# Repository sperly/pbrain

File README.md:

# PocketBrain VS Code handoff

Open this folder in VS Code. The [project plan](docs/PocketBrain_Project_Plan.md)
covers the hardware, controls, account model, and firmware behavior.

| Path | What it contains |
|---|---|
| [backend](backend/README.md) | PHP 8.4 dashboard, device API, Realtime client-secret endpoint, and MariaDB migrations |
| [desktop](desktop/README.md) | Python/Tk simulator, microphone and speaker routing, and the direct Realtime client |
| [embedded](embedded/README.md) | CMake/ESP-IDF firmware, bench wiring, and host tests for ESP32-S3 |

This workspace folds the desktop ZIP's PHP add-on into the backend. There
is one PHP API entry point. Existing deployments can deploy this source
while retaining their private configuration and database.

## First development session

1. Run the desktop app in **Demo**, then **Loopback**, using its README.
2. Set up the PHP backend on the HTTPS host. On a fresh database, import
   all four SQL migrations in order. On existing databases, import only
   migrations that have not run, including `003_user_openai_keys.sql` and `004_legal_acceptances.sql`.
   Set DB credentials and a stable application key in the private config.
   Each user adds their OpenAI API key through the dashboard; shared site
   billing requires an explicit opt-in setting.
3. Sign in, pair the desktop simulator, and try one spoken and one muted
   question in **Live**. Check that unlinking the device blocks subsequent
   credential requests.
4. Verify shared conversation history in Live mode. Save a turn, restart the
   simulator, and continue it from History. Pair a second device under the same
   account and check shared history with separate active selections. Disconnect
   after receiving a reply and confirm **Retry save** does not generate another
   answer. Delete a thread and confirm it disappears after the other device syncs.

## Device interface

All paths below are relative to the configured HTTPS base URL. The request
credential is sent in the Authorization bearer header where specified.

| Method and action on api.php | Credential | Current response |
|---|---|---|
| POST pair-start | None | 201 with code, polling_secret, expires_in, poll_interval, and verification_uri |
| POST pair-poll | Polling secret | 202 while awaiting approval, 200 with device_credential when linked, 404 when expired or unknown |
| GET device | Device credential | 200 with id and name, 401 for an invalid or revoked credential |
| POST realtime-secret | Device credential | 200 with value, expires_at, and model, 401 for an invalid or revoked credential |

The simulator records into a 24 kHz, 16-bit mono PCM buffer and opens a new
Realtime WebSocket per turn after Talk is released. Live conversation history
and device selections sync through PHP; each profile keeps a local cache and
one pending recording or completed transcript. Demo and Loopback stay local.
See the backend README for the conversation API and integration tests.

## Verification carried forward

The desktop UI was exercised in Tk. Realtime events and PCM processing
were exercised with mocks. Invite, ownership, and pairing SQL behavior
was checked using a SQLite translation. The PHP 8.4/MariaDB integration,
physical audio devices, and a live OpenAI exchange still need to be
verified on the deployment host and desktop.

ESP-IDF firmware is now in [embedded](embedded/README.md), with build
instructions, configurable bench wiring, and host tests. Physical firmware
validation, custom PCB and enclosure CAD remain subsequent milestones.

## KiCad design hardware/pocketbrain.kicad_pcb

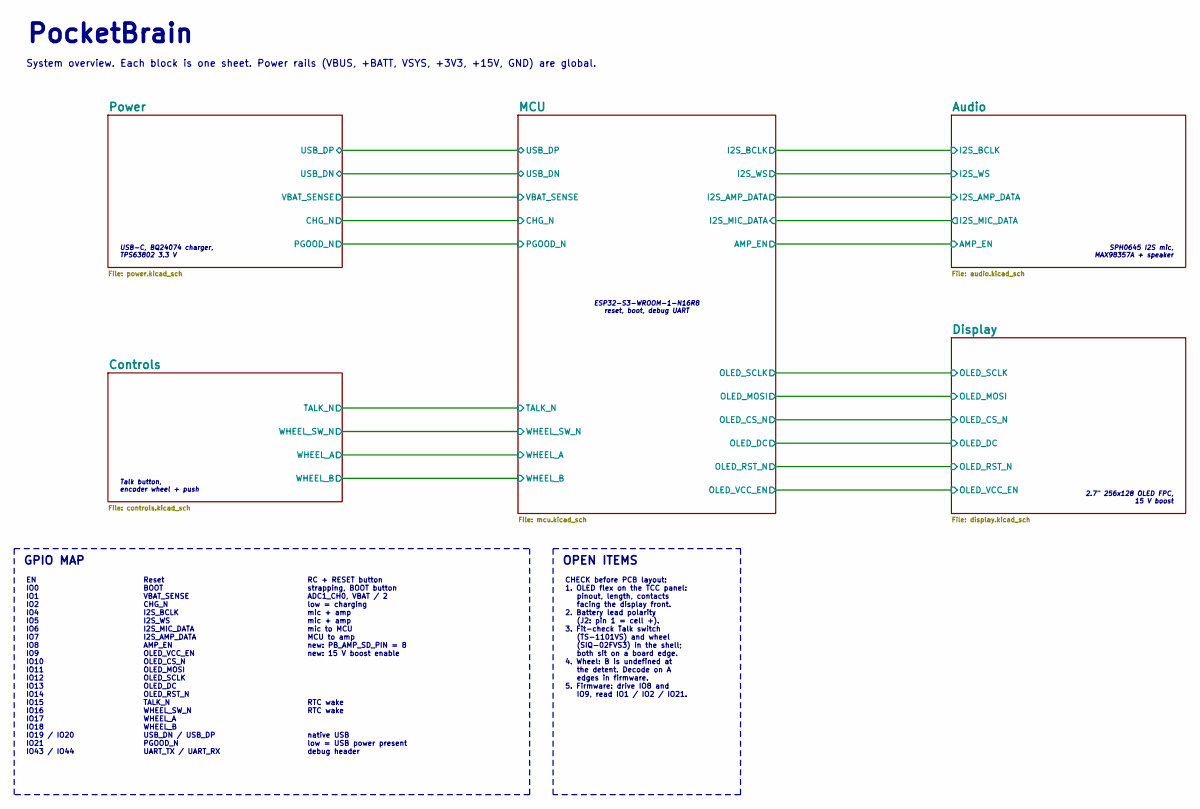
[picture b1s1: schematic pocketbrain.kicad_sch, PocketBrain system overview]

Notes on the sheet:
USB-C, BQ24074 charger, TPS63802 3.3 V
ESP32-S3-WROOM-1-N16R8 reset, boot, debug UART
CHECK before PCB layout: 1. OLED flex on the TCC panel: pinout, length, contacts facing the display front. 2. Battery lead polarity (J2: pin 1 = cell +). 3. Fit-check Talk switch (TS-1101VS) and wheel (SIQ-02FVS3) in the shell; both sit on a board edge. 4. Wheel: B is undefined at the detent. Decod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
Reset BOOT VBAT_SENSE CHG_N I2S_BCLK I2S_WS I2S_MIC_DATA I2S_AMP_DATA AMP_EN OLED_VCC_EN OLED_CS_N OLED_MOSI OLED_SCLK OLED_DC OLED_RST_N TALK_N WHEEL_SW_N WHEEL_A WHEEL_B USB_DN / USB_DP PGOOD_N UART_TX / UART_RX
Talk button, encoder wheel + push
RC + RESET button strapping, BOOT button ADC1_CH0, VBAT / 2 low = charging mic + amp mic + amp mic to MCU MCU to amp new: PB_AMP_SD_PIN = 8 new: 15 V boost enable RTC wake RTC wake native USB low = USB power present debug header
System overview. Each block is one sheet. Power rails (VBUS, +BATT, VSYS, +3V3, +15V, GND) are global.
2.7" 256x128 OLED FPC, 15 V boost
OPEN ITEMS
GPIO MAP
EN IO0 IO1 IO2 IO4 IO5 IO6 IO7 IO8 IO9 IO10 IO11 IO12 IO13 IO14 IO15 IO16 IO17 IO18 IO19 / IO20 IO21 IO43 / IO44
PocketBrain
SPH0645 I2S mic, MAX98357A + speaker

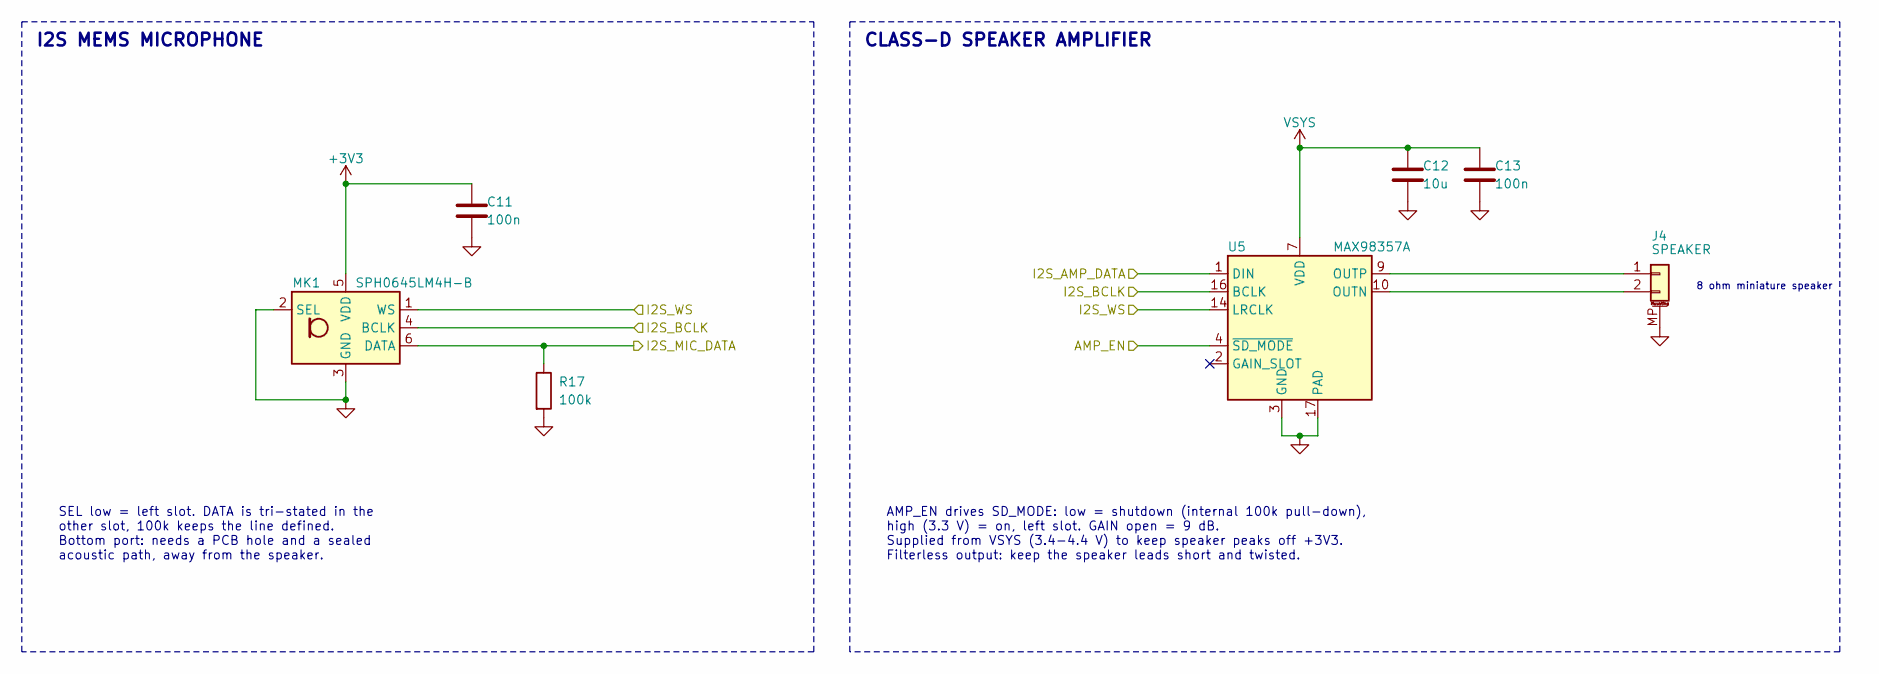
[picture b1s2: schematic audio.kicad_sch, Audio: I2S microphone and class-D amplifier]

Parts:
C11, C13: 100n; C_0402_1005Metric
C12: 10u; C_0603_1608Metric
J4: SPEAKER; JST_SH_BM02B-SRSS-TB_1x02-1MP_P1.00mm_Vertical
MK1: SPH0645LM4H-B; Knowles_SPH0645LM4H-6_3.5x2.65mm
R17: 100k; R_0402_1005Metric
U5: MAX98357A; TQFN-16-1EP_3x3mm_P0.5mm_EP1.23x1.23mm

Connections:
+3V3: C11.1, MK1.5 (VDD); also elsewhere on the board
/Audio/AMP_EN: U5.4 (~SD_MODE); also elsewhere on the board
/Audio/I2S_AMP_DATA: U5.1 (DIN); also elsewhere on the board
/Audio/I2S_BCLK: MK1.4 (BCLK), U5.16 (BCLK); also elsewhere on the board
/Audio/I2S_MIC_DATA: MK1.6 (DATA), R17.1; also elsewhere on the board
/Audio/I2S_WS: MK1.1 (WS), U5.14 (LRCLK); also elsewhere on the board
GND: C11.2, C12.2, C13.2, J4.MP (MountPin), MK1.2 (SEL), MK1.3 (GND), R17.2, U5.3 (GND), U5.11 (GND), U5.15 (GND), U5.17 (PAD); also elsewhere on the board
unnamed: J4.1, U5.9 (OUTP)
unnamed: J4.2, U5.10 (OUTN)
VSYS: C12.1, C13.1, U5.7 (VDD), U5.8 (VDD); also elsewhere on the board

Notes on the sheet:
CLASS-D SPEAKER AMPLIFIER
AMP_EN drives SD_MODE: low = shutdown (internal 100k pull-down), high (3.3 V) = on, left slot. GAIN open = 9 dB. Supplied from VSYS (3.4-4.4 V) to keep speaker peaks off +3V3. Filterless output: keep the speaker leads short and twisted.
8 ohm miniature speaker
I2S MEMS MICROPHONE
SEL low = left slot. DATA is tri-stated in the other slot, 100k keeps the line defined. Bottom port: needs a PCB hole and a sealed acoustic path, away from the speaker.

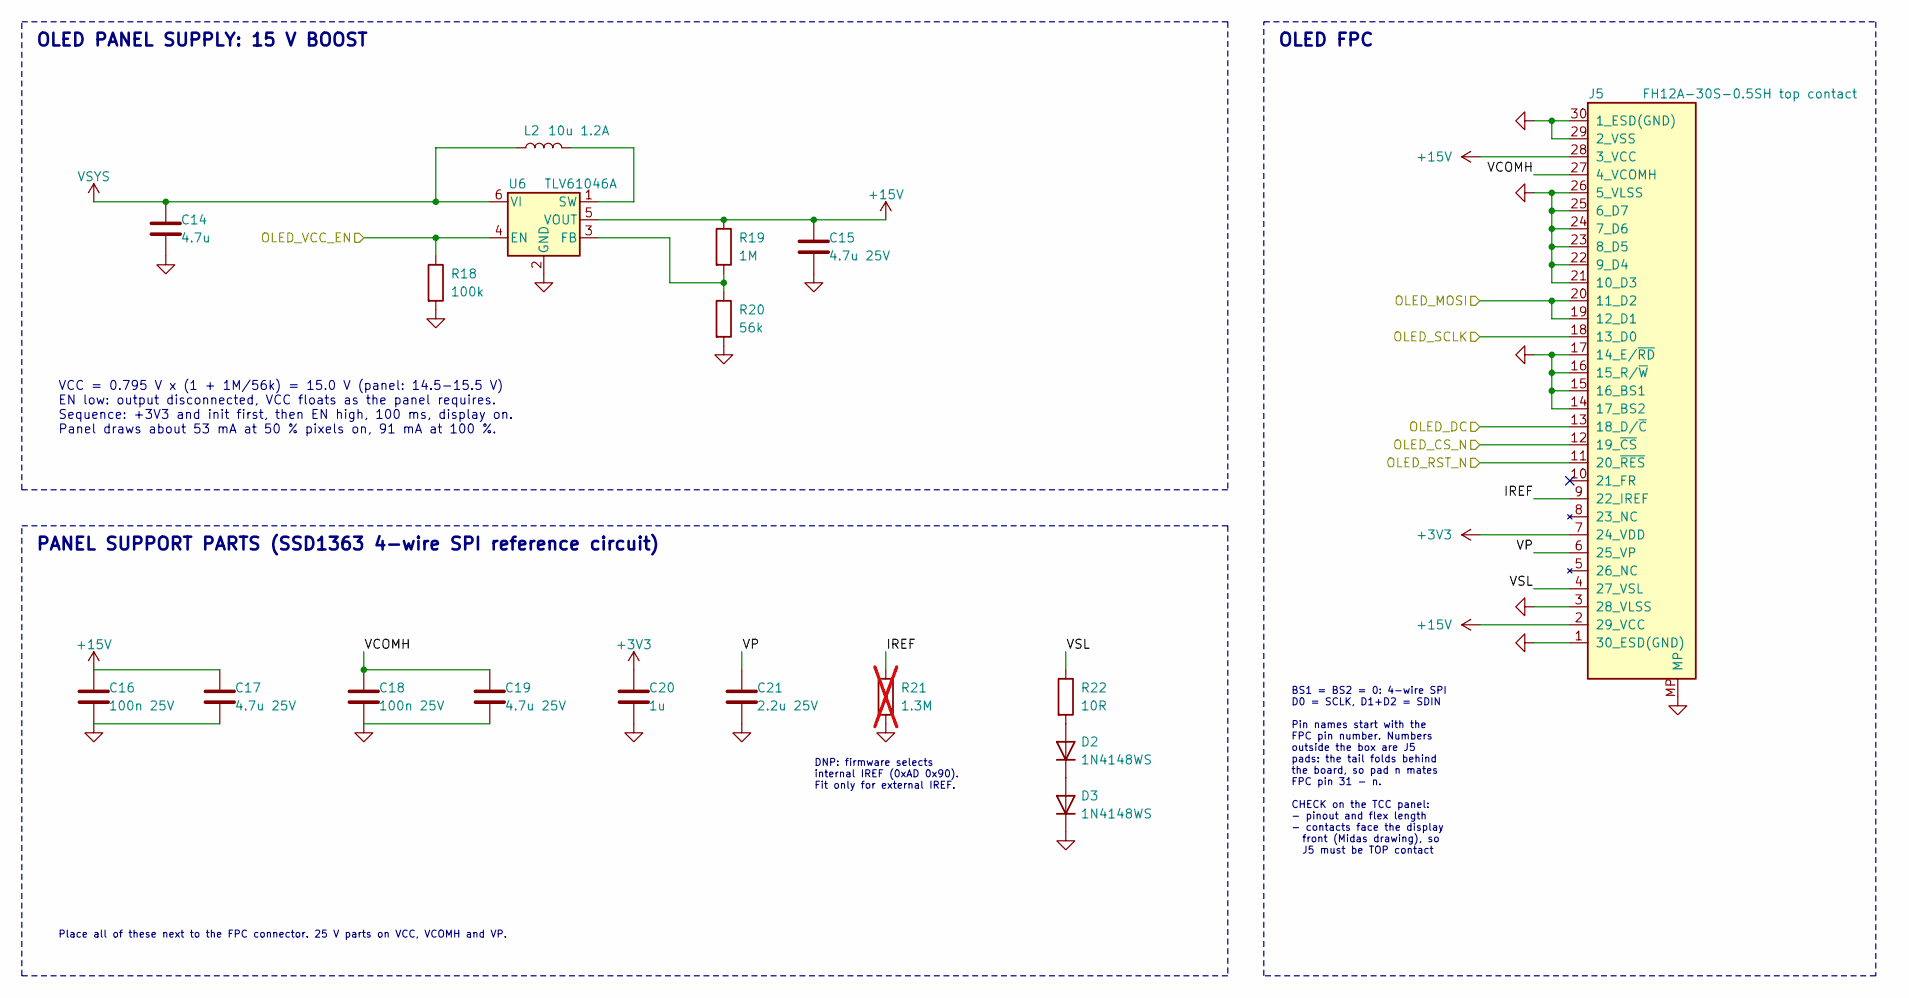
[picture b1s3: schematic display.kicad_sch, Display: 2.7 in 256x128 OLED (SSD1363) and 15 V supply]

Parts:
C14: 4.7u; C_0603_1608Metric
C15, C17, C19: 4.7u 25V; C_0805_2012Metric
C16, C18: 100n 25V; C_0402_1005Metric
C20: 1u; C_0402_1005Metric
C21: 2.2u 25V; C_0603_1608Metric
D2, D3: 1N4148WS; D_SOD-323
J5: FH12A-30S-0.5SH top contact; Hirose_FH12-30S-0.5SH_1x30-1MP_P0.50mm_Horizontal; MPN FH12A-30S-0.5SH(55); LCSC C3036214
L2: 10u 1.2A; L_Taiyo-Yuden_NR-30xx
R18: 100k; R_0402_1005Metric
R19: 1M; R_0402_1005Metric
R20: 56k; R_0402_1005Metric
R21: 1.3M; R_0402_1005Metric; not fitted
R22: 10R; R_0402_1005Metric
U6: TLV61046A; SOT-23-6

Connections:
+3V3: C20.1, J5.7 (24_VDD); also elsewhere on the board
+15V: C15.1, C16.1, C17.1, J5.2 (29_VCC), J5.28 (3_VCC), R19.1, U6.5 (VOUT)
/Display/IREF: J5.9 (22_IREF), R21.1
/Display/OLED_CS_N: J5.12 (19_~CS); also elsewhere on the board
/Display/OLED_DC: J5.13 (18_D/~C); also elsewhere on the board
/Display/OLED_MOSI: J5.19 (12_D1), J5.20 (11_D2); also elsewhere on the board
/Display/OLED_RST_N: J5.11 (20_~RES); also elsewhere on the board
/Display/OLED_SCLK: J5.18 (13_D0); also elsewhere on the board
/Display/OLED_VCC_EN: R18.1, U6.4 (EN); also elsewhere on the board
/Display/VCOMH: C18.1, C19.1, J5.27 (4_VCOMH)
/Display/VP: C21.1, J5.6 (25_VP)
/Display/VSL: J5.4 (27_VSL), R22.1
GND: C14.2, C15.2, C16.2, C17.2, C18.2, C19.2, C20.2, C21.2, D3.1 (K), J5.1 (30_ESD(GND)), J5.3 (28_VLSS), J5.14 (17_BS2), J5.15 (16_BS1), J5.16 (15_R/~W), J5.17 (14_E/~RD), J5.21 (10_D3), J5.22 (9_D4), J5.23 (8_D5), J5.24 (7_D6), J5.25 (6_D7), J5.26 (5_VLSS), J5.29 (2_VSS), J5.30 (1_ESD(GND)), J5.MP, R18.2, R20.2, R21.2, U6.2 (GND); also elsewhere on the board
unnamed: D2.2 (A), R22.2
unnamed: D2.1 (K), D3.2 (A)
unnamed: R19.2, R20.1, U6.3 (FB)
unnamed: L2.2, U6.1 (SW)
VSYS: C14.1, L2.1, U6.6 (VI); also elsewhere on the board

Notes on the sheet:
PANEL SUPPORT PARTS (SSD1363 4-wire SPI reference circuit)
Place all of these next to the FPC connector. 25 V parts on VCC, VCOMH and VP.
BS1 = BS2 = 0: 4-wire SPI D0 = SCLK, D1+D2 = SDIN Pin names start with the FPC pin number. Numbers outside the box are J5 pads: the tail folds behind the board, so pad n mates FPC pin 31 - n. CHECK on the TCC panel: - pinout and flex length - contacts face the display front (Midas drawing), so J5 m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
VCC = 0.795 V x (1 + 1M/56k) = 15.0 V (panel: 14.5-15.5 V) EN low: output disconnected, VCC floats as the panel requires. Sequence: +3V3 and init first, then EN high, 100 ms, display on. Panel draws about 53 mA at 50 % pixels on, 91 mA at 100 %.
DNP: firmware selects internal IREF (0xAD 0x90). Fit only for external IREF.
OLED PANEL SUPPLY: 15 V BOOST
OLED FPC

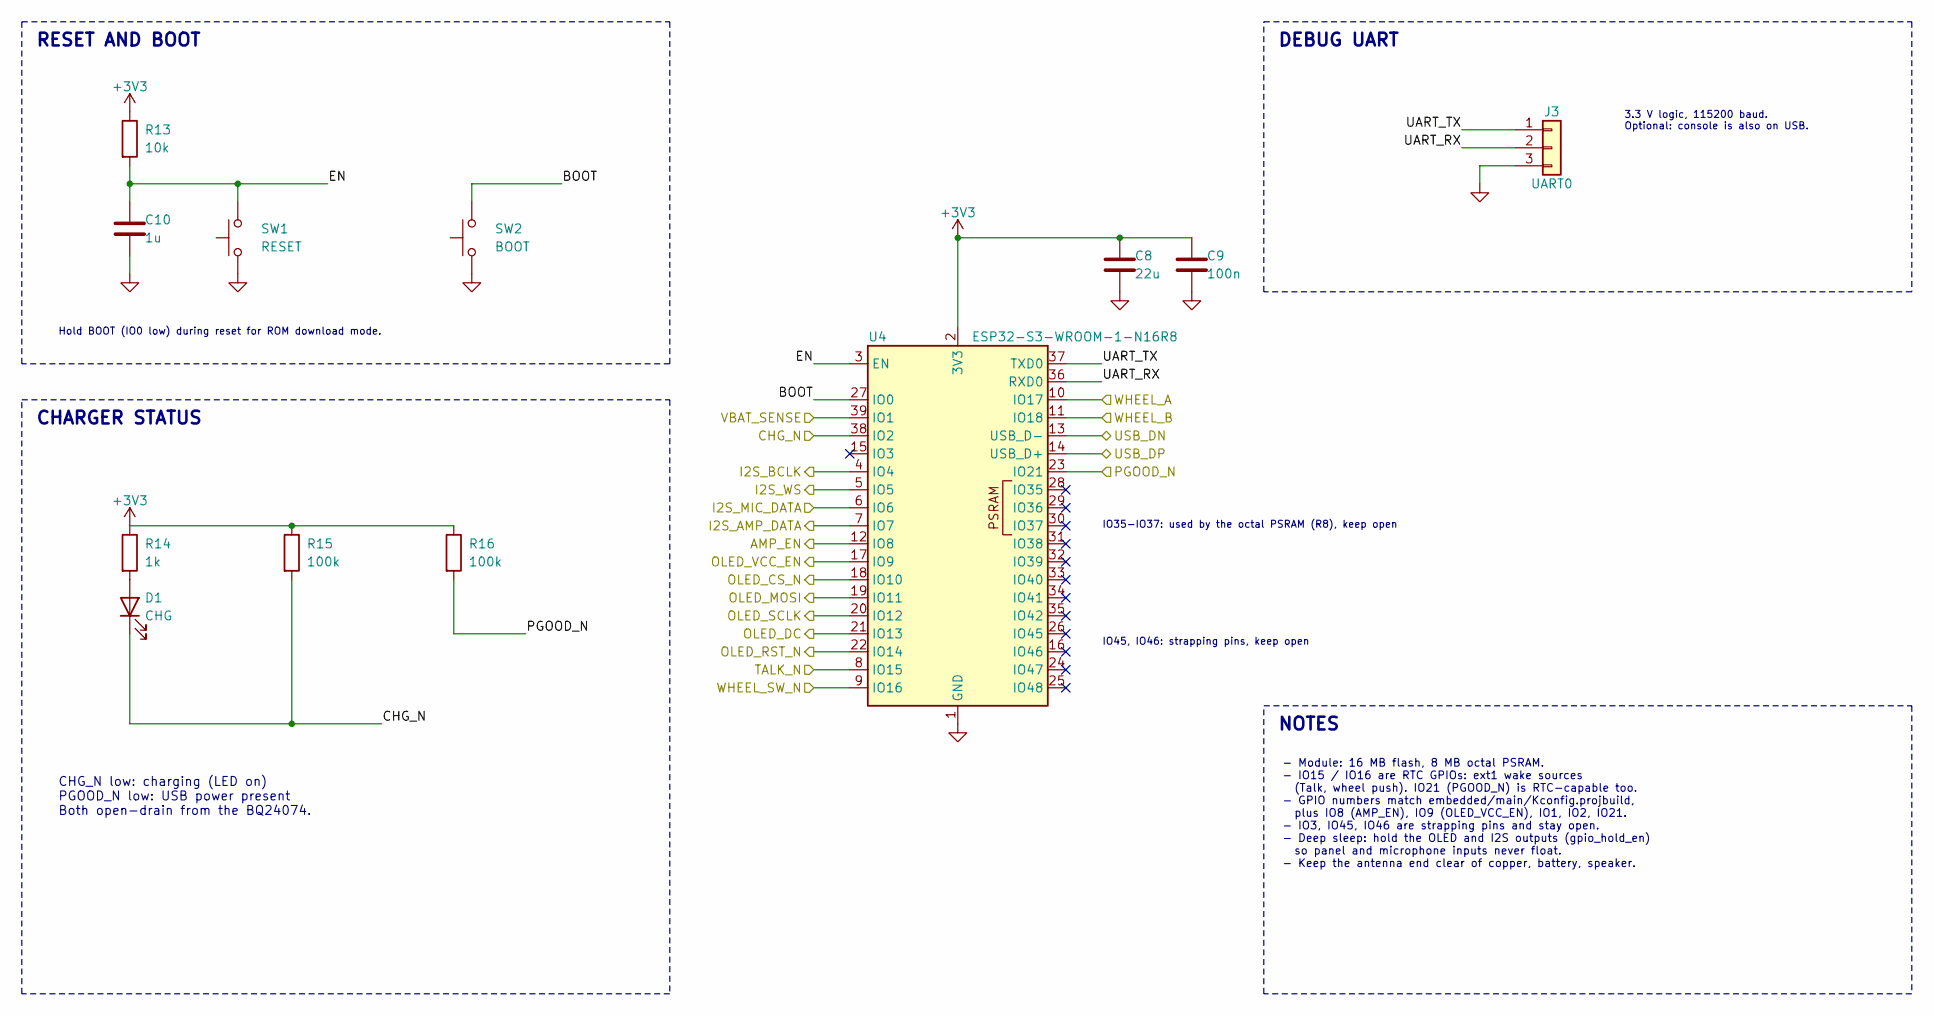
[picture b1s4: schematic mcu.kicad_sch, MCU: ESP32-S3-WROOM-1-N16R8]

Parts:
C8: 22u; C_0805_2012Metric
C9: 100n; C_0402_1005Metric
C10: 1u; C_0402_1005Metric
D1: CHG; LED_0603_1608Metric
J3: UART0; PinHeader_1x03_P1.27mm_Vertical
R13: 10k; R_0402_1005Metric
R14: 1k; R_0402_1005Metric
R15, R16: 100k; R_0402_1005Metric
SW1: RESET; SW_SPST_B3U-1000P
SW2: BOOT; SW_SPST_B3U-1000P
U4: ESP32-S3-WROOM-1-N16R8; ESP32-S3-WROOM-1

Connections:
+3V3: C8.1, C9.1, R13.1, R14.1, R15.1, R16.1, U4.2 (3V3); also elsewhere on the board
/Audio/AMP_EN: U4.12 (IO8); also elsewhere on the board
/Audio/I2S_AMP_DATA: U4.7 (IO7); also elsewhere on the board
/Audio/I2S_BCLK: U4.4 (IO4); also elsewhere on the board
/Audio/I2S_MIC_DATA: U4.6 (IO6); also elsewhere on the board
/Audio/I2S_WS: U4.5 (IO5); also elsewhere on the board
/Controls/TALK_N: U4.8 (IO15); also elsewhere on the board
/Controls/WHEEL_A: U4.10 (IO17); also elsewhere on the board
/Controls/WHEEL_B: U4.11 (IO18); also elsewhere on the board
/Controls/WHEEL_SW_N: U4.9 (IO16); also elsewhere on the board
/Display/OLED_CS_N: U4.18 (IO10); also elsewhere on the board
/Display/OLED_DC: U4.21 (IO13); also elsewhere on the board
/Display/OLED_MOSI: U4.19 (IO11); also elsewhere on the board
/Display/OLED_RST_N: U4.22 (IO14); also elsewhere on the board
/Display/OLED_SCLK: U4.20 (IO12); also elsewhere on the board
/Display/OLED_VCC_EN: U4.17 (IO9); also elsewhere on the board
/MCU/BOOT: SW2.2, U4.27 (IO0)
/MCU/CHG_N: D1.1 (K), R15.2, U4.38 (IO2); also elsewhere on the board
/MCU/EN: C10.1, R13.2, SW1.2, U4.3 (EN)
/MCU/PGOOD_N: R16.2, U4.23 (IO21); also elsewhere on the board
/MCU/UART_RX: J3.2, U4.36 (RXD0)
/MCU/UART_TX: J3.1, U4.37 (TXD0)
/MCU/USB_DN: U4.13 (USB_D-); also elsewhere on the board
/MCU/USB_DP: U4.14 (USB_D+); also elsewhere on the board
/MCU/VBAT_SENSE: U4.39 (IO1); also elsewhere on the board
GND: C8.2, C9.2, C10.2, J3.3, SW1.1, SW2.1, U4.1 (GND), U4.40 (GND), U4.41 (GND); also elsewhere on the board
unnamed: D1.2 (A), R14.2

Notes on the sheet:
CHARGER STATUS
Hold BOOT (IO0 low) during reset for ROM download mode.
CHG_N low: charging (LED on) PGOOD_N low: USB power present Both open-drain from the BQ24074.
3.3 V logic, 115200 baud. Optional: console is also on USB.
NOTES
RESET AND BOOT
DEBUG UART
IO35-IO37: used by the octal PSRAM (R8), keep open
IO45, IO46: strapping pins, keep open
- Module: 16 MB flash, 8 MB octal PSRAM. - IO15 / IO16 are RTC GPIOs: ext1 wake sources (Talk, wheel push). IO21 (PGOOD_N) is RTC-capable too. - GPIO numbers match embedded/main/Kconfig.projbuild, plus IO8 (AMP_EN), IO9 (OLED_VCC_EN), IO1, IO2, IO21. - IO3, IO45, IO46 are strapping pins and stay op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

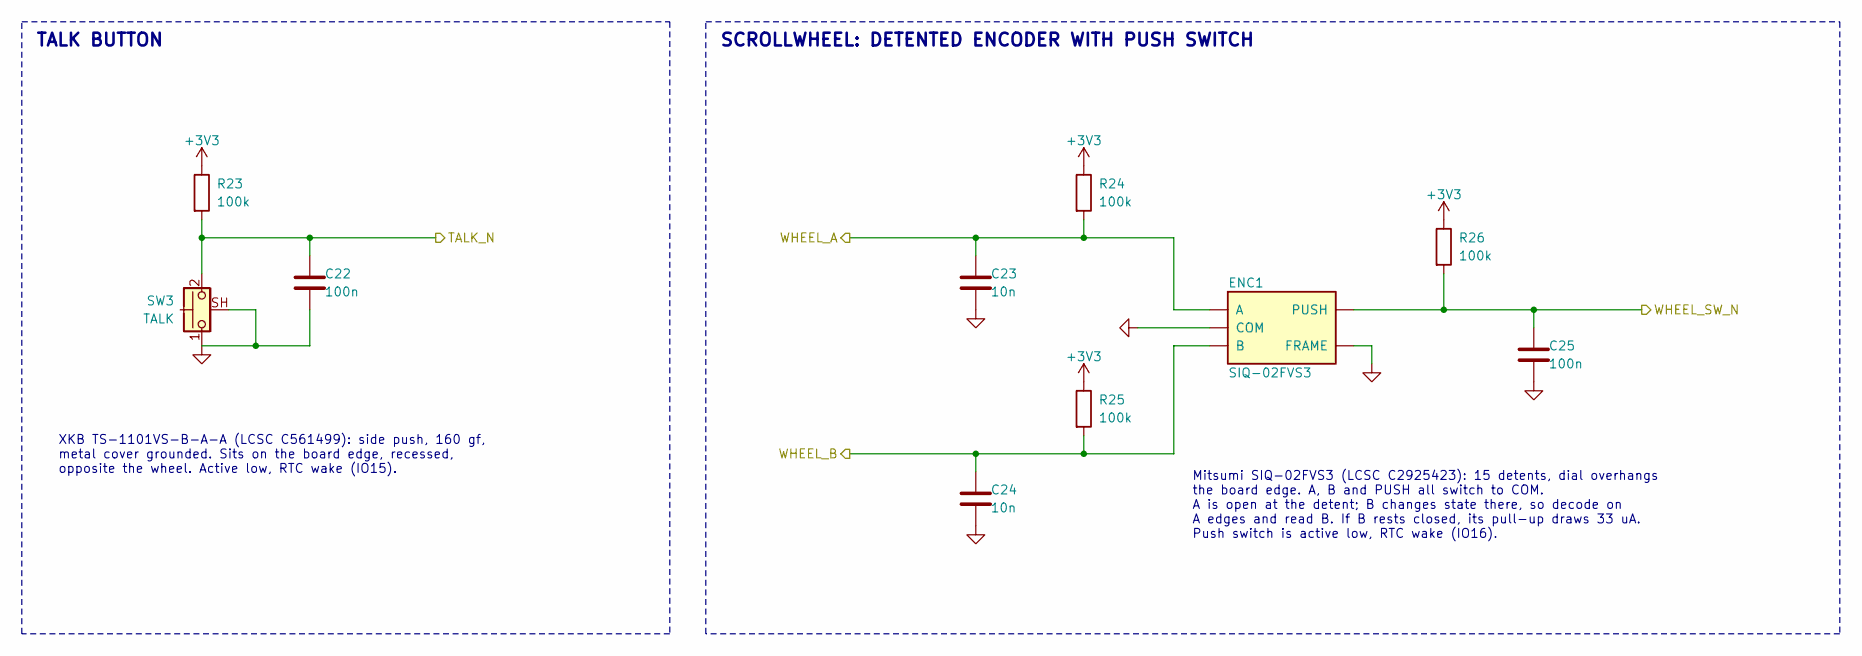
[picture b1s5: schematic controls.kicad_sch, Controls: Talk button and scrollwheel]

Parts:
C22, C25: 100n; C_0402_1005Metric
C23, C24: 10n; C_0402_1005Metric
ENC1: SIQ-02FVS3; RotaryEncoder_Mitsumi_SIQ-02FVS3; MPN SIQ-02FVS3; LCSC C2925423
R23, R24, R25, R26: 100k; R_0402_1005Metric
SW3: TALK; SW_XKB_TS-1101VS_SidePush; MPN TS-1101VS-B-A-A; LCSC C561499

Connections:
+3V3: R23.1, R24.1, R25.1, R26.1; also elsewhere on the board
/Controls/TALK_N: C22.1, R23.2, SW3.2; also elsewhere on the board
/Controls/WHEEL_A: C23.1, ENC1.A, R24.2; also elsewhere on the board
/Controls/WHEEL_B: C24.1, ENC1.B, R25.2; also elsewhere on the board
/Controls/WHEEL_SW_N: C25.1, ENC1.S (PUSH), R26.2; also elsewhere on the board
GND: C22.2, C23.2, C24.2, C25.2, ENC1.C (COM), ENC1.MP (FRAME), SW3.1, SW3.SH (B); also elsewhere on the board

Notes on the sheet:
SCROLLWHEEL: DETENTED ENCODER WITH PUSH SWITCH
TALK BUTTON
Mitsumi SIQ-02FVS3 (LCSC C2925423): 15 detents, dial overhangs the board edge. A, B and PUSH all switch to COM. A is open at the detent; B changes state there, so decode on A edges and read B. If B rests closed, its pull-up draws 33 uA. Push switch is active low, RTC wake (IO16).
XKB TS-1101VS-B-A-A (LCSC C561499): side push, 160 gf, metal cover grounded. Sits on the board edge, recessed, opposite the wheel. Active low, RTC wake (IO15).

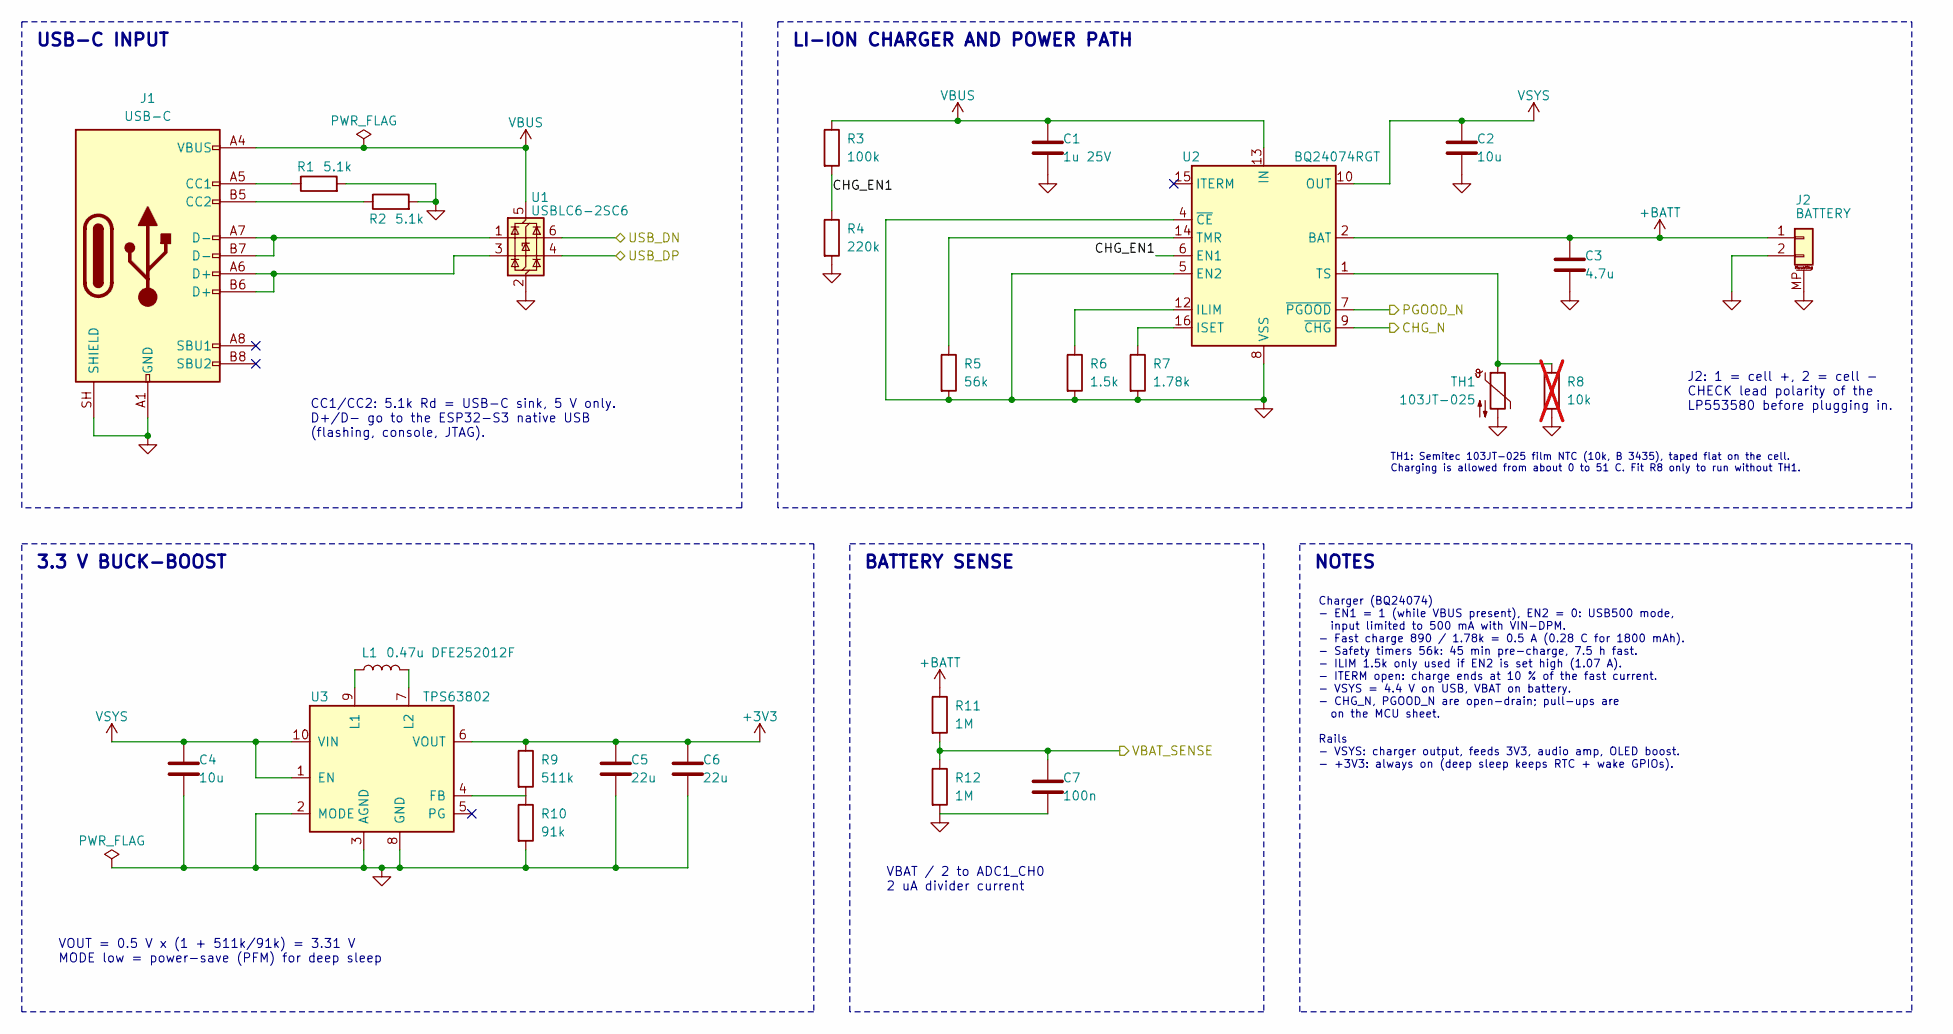
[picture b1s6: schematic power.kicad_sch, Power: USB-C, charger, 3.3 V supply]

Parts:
C1: 1u 25V; C_0603_1608Metric
C2, C4: 10u; C_0603_1608Metric
C3: 4.7u; C_0603_1608Metric
C5, C6: 22u; C_0805_2012Metric
C7: 100n; C_0402_1005Metric
J1: USB-C; USB_C_Receptacle_GCT_USB4105-xx-A_16P_TopMnt_Horizontal
J2: BATTERY; JST_PH_B2B-PH-SM4-TB_1x02-1MP_P2.00mm_Vertical
L1: 0.47u DFE252012F; L_Murata_DFE252012; MPN DFE252012F-R47M=P2; LCSC C703140
R1, R2: 5.1k; R_0402_1005Metric
R3: 100k; R_0402_1005Metric
R4: 220k; R_0402_1005Metric
R5: 56k; R_0402_1005Metric
R6: 1.5k; R_0402_1005Metric
R7: 1.78k; R_0402_1005Metric
R8: 10k; R_0402_1005Metric; not fitted
R9: 511k; R_0402_1005Metric
R10: 91k; R_0402_1005Metric
R11, R12: 1M; R_0402_1005Metric
TH1: 103JT-025; Thermistor_Semitec_JT_Leads_P1.8mm; MPN 103JT-025
U1: USBLC6-2SC6; SOT-23-6
U2: BQ24074RGT; VQFN-16-1EP_3x3mm_P0.5mm_EP1.6x1.6mm
U3: TPS63802; Texas_DLA0010A_VSON-HR-10_2x3mm_P0.5mm; MPN TPS63802DLAR; LCSC C2845237

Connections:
+3V3: C5.1, C6.1, R9.1, U3.6 (VOUT); also elsewhere on the board
+BATT: C3.1, J2.1, R11.1, U2.2 (BAT), U2.3 (BAT)
/MCU/CHG_N: U2.9 (~CHG); also elsewhere on the board
/MCU/PGOOD_N: U2.7 (~PGOOD); also elsewhere on the board
/MCU/USB_DN: U1.6 (I/O1); also elsewhere on the board
/MCU/USB_DP: U1.4 (I/O2); also elsewhere on the board
/MCU/VBAT_SENSE: C7.1, R11.2, R12.1; also elsewhere on the board
/Power/CHG_EN1: R3.2, R4.1, U2.6 (EN1)
GND: C1.2, C2.2, C3.2, C4.2, C5.2, C6.2, C7.2, J1.A1 (GND), J1.A12 (GND), J1.B1 (GND), J1.B12 (GND), J1.SH (SHIELD), J2.2, J2.MP (MountPin), R1.2, R2.2, R4.2, R5.2, R6.2, R7.2, R8.2, R10.2, R12.2, TH1.2, U1.2 (GND), U2.4 (~CE), U2.5 (EN2), U2.8 (VSS), U2.17 (VSS), U3.2 (MODE), U3.3 (AGND), U3.8 (GND); also elsewhere on the board
unnamed: J1.A5 (CC1), R1.1
unnamed: J1.B5 (CC2), R2.1
unnamed: J1.A6 (D+), J1.B6 (D+), U1.3 (I/O2)
unnamed: J1.A7 (D-), J1.B7 (D-), U1.1 (I/O1)
unnamed: R6.1, U2.12 (ILIM)
unnamed: R7.1, U2.16 (ISET)
unnamed: R5.1, U2.14 (TMR)
unnamed: R8.1, TH1.1, U2.1 (TS)
unnamed: R9.2, R10.1, U3.4 (FB)
unnamed: L1.1, U3.9 (L1)
unnamed: L1.2, U3.7 (L2)
VBUS: C1.1, J1.A4 (VBUS), J1.A9 (VBUS), J1.B4 (VBUS), J1.B9 (VBUS), R3.1, U1.5 (VBUS), U2.13 (IN)
VSYS: C2.1, C4.1, U2.10 (OUT), U2.11 (OUT), U3.1 (EN), U3.10 (VIN); also elsewhere on the board

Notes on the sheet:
J2: 1 = cell +, 2 = cell - CHECK lead polarity of the LP553580 before plugging in.
LI-ION CHARGER AND POWER PATH
3.3 V BUCK-BOOST
VBAT / 2 to ADC1_CH0 2 uA divider current
CC1/CC2: 5.1k Rd = USB-C sink, 5 V only. D+/D- go to the ESP32-S3 native USB (flashing, console, JTAG).
TH1: Semitec 103JT-025 film NTC (10k, B 3435), taped flat on the cell. Charging is allowed from about 0 to 51 C. Fit R8 only to run without TH1.
BATTERY SENSE
USB-C INPUT
Charger (BQ24074) - EN1 = 1 (while VBUS present), EN2 = 0: USB500 mode, input limited to 500 mA with VIN-DPM. - Fast charge 890 / 1.78k = 0.5 A (0.28 C for 1800 mAh). - Safety timers 56k: 45 min pre-charge, 7.5 h fast. - ILIM 1.5k only used if EN2 is set high (1.07 A). - ITERM open: charge ends at 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
NOTES
VOUT = 0.5 V x (1 + 511k/91k) = 3.31 V MODE low = power-save (PFM) for deep sleep

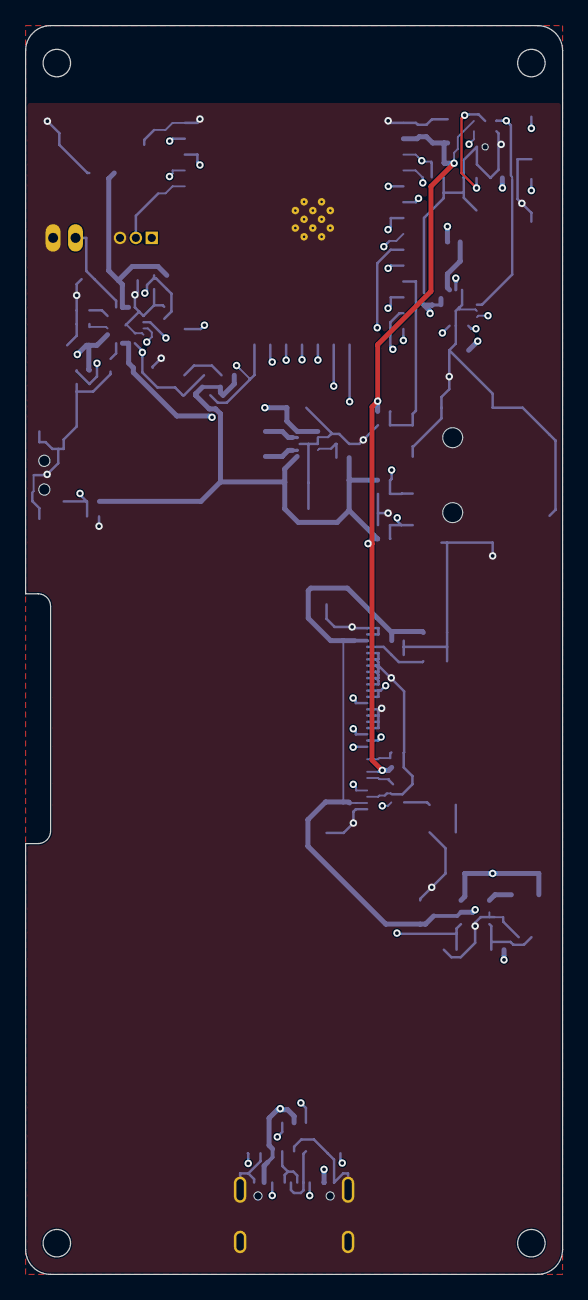
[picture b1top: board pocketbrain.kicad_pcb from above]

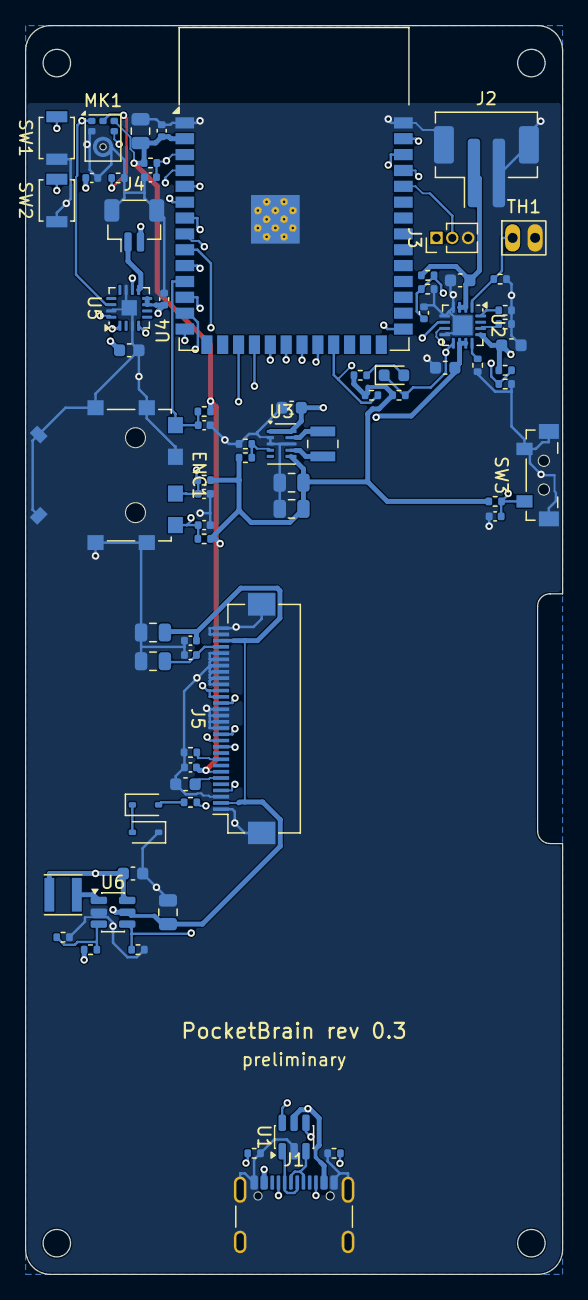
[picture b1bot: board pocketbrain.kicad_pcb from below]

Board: 4 copper layers, 43.0 x 100.0 mm, 73 parts (73 on the bottom side), 53 nets.
